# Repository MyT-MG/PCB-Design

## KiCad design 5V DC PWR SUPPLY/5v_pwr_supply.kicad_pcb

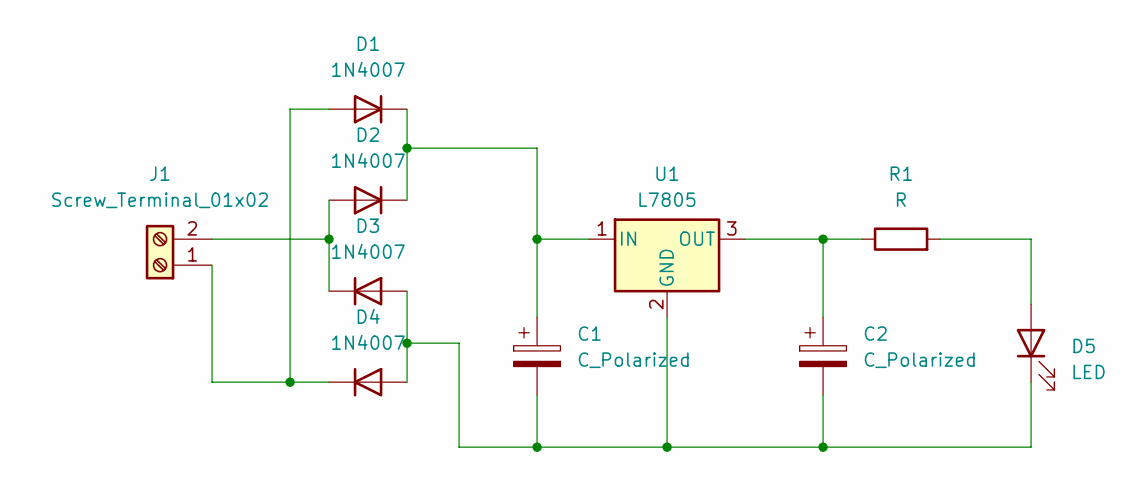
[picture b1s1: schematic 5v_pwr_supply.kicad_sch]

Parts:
C1, C2: C_Polarized; CP_Radial_D8.0mm_P5.00mm
D1, D2, D3, D4: 1N4007; D_DO-41_SOD81_P10.16mm_Horizontal
D5: LED; LED_D5.0mm
J1: Screw_Terminal_01x02; TerminalBlock_MaiXu_MX126-5.0-02P_1x02_P5.00mm
R1: R; R_Axial_DIN0204_L3.6mm_D1.6mm_P7.62mm_Horizontal
U1: L7805; TO-220-3_Vertical

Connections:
unnamed: D1.2 (A), D4.1 (K), J1.1
unnamed: C1.1, D1.1 (K), D2.1 (K), U1.1 (IN)
unnamed: D2.2 (A), D3.1 (K), J1.2
unnamed: C1.2, C2.2, D3.2 (A), D4.2 (A), D5.1 (K), U1.2 (GND)
unnamed: D5.2 (A), R1.2
unnamed: C2.1, R1.1, U1.3 (OUT)

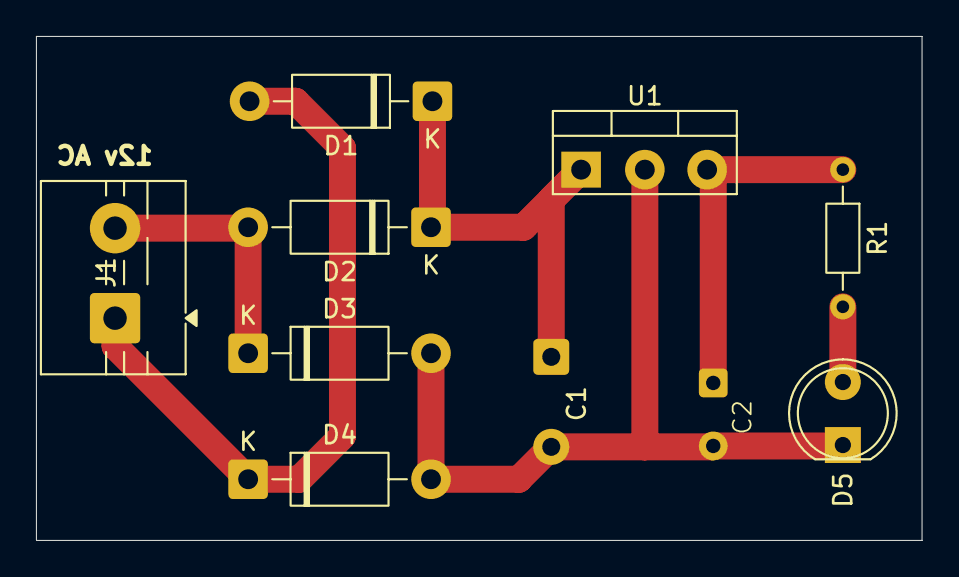
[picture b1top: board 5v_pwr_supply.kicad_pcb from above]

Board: 2 copper layers, 49.2 x 28.0 mm, 10 parts (0 on the bottom side), 6 nets.

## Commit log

2025-10-17 Add description for 5V DC power supply project
2025-10-17 Added KiCAD project files and output pcb layout
